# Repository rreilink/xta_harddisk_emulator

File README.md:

# xta_harddisk_emulator
A replacement of old XTA harddisks by USB or SPI-flash storage

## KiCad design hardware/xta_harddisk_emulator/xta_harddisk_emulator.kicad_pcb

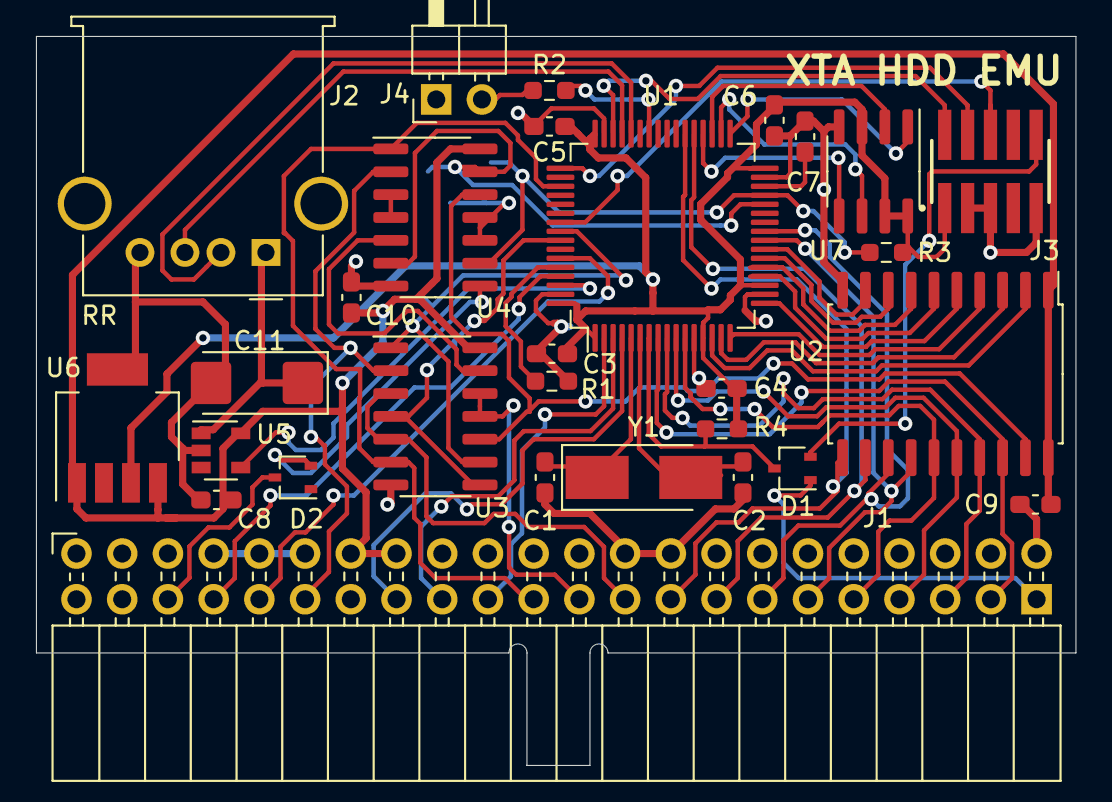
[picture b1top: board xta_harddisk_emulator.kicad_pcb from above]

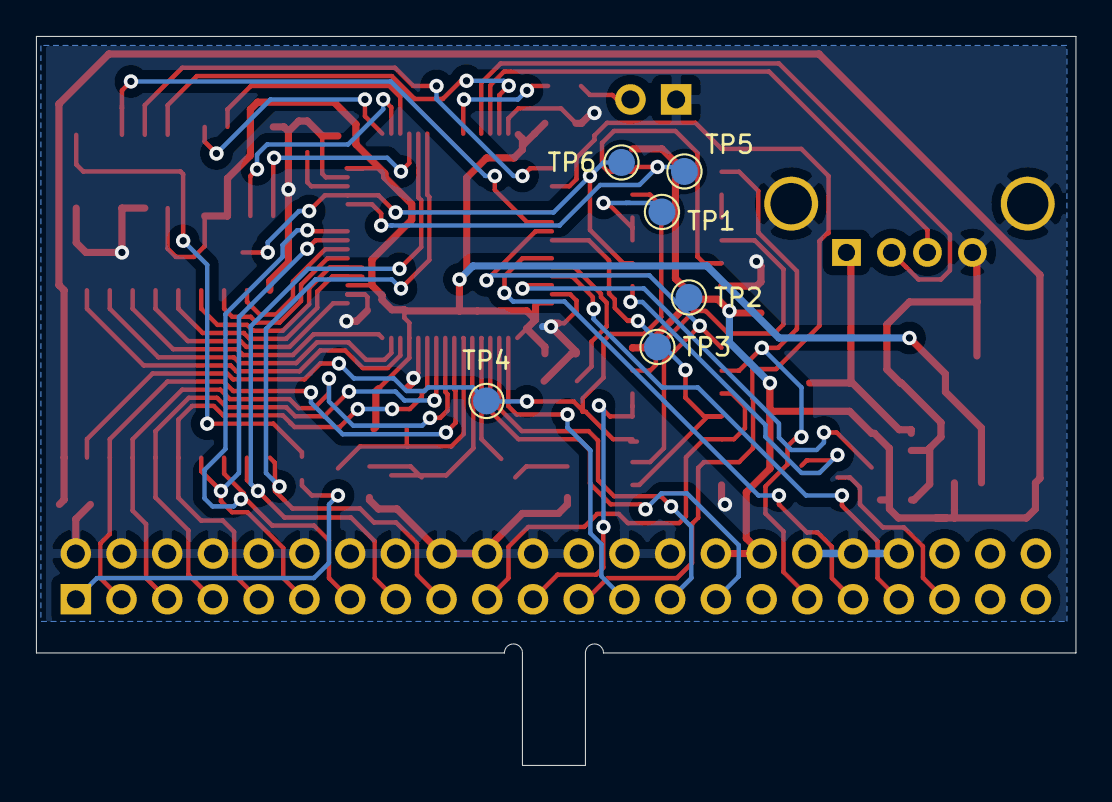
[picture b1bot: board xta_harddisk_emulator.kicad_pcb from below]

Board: 2 copper layers, 57.7 x 40.5 mm, 35 parts (6 on the bottom side), 58 nets.

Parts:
C1, C2: 18pF; C_0603_1608Metric_Pad1.08x0.95mm_HandSolder
C3, C4, C5, C6, C9, C10: 100n; C_0603_1608Metric_Pad1.08x0.95mm_HandSolder
C7, C8: 4.7u; C_0603_1608Metric_Pad1.08x0.95mm_HandSolder
C11: 150u; CP_EIA-6032-28_Kemet-C_Pad2.25x2.35mm_HandSolder
D1, D2: BAT54A; SOT-323_SC-70
J1: Conn_02x22_Odd_Even; PinSocket_2x22_P2.54mm_Horizontal
J2: USB_A; USB_A_Molex_67643_Horizontal
J3: Conn_ARM_JTAG_SWD_10; SAMTEC_FTSH-105-XX-X-DV
J4: Conn_01x02_Male; PinHeader_1x02_P2.54mm_Horizontal
R1, R3, R4: 10k; R_0603_1608Metric_Pad0.98x0.95mm_HandSolder
R2: 220; R_0603_1608Metric_Pad0.98x0.95mm_HandSolder
TP1, TP2, TP3, TP4, TP5, TP6: TestPoint; TestPoint_Pad_D1.5mm
U1: STM32F446RETx; LQFP-64_10x10mm_P0.5mm
U2: 74LS245; SOIC-20W_7.5x12.8mm_P1.27mm
U3: 7402; SOIC-14_3.9x8.7mm_P1.27mm
U4: 7400; SOIC-14_3.9x8.7mm_P1.27mm
U5: TPS2051B; SOT-23-5
U6: LP38693MP-3.3; SOT-223-5
U7: S25FL127SABMFI101; SOIC-8_3.9x4.9mm_P1.27mm
Y1: 8MHz; Crystal_SMD_5032-2Pin_5.0x3.2mm_HandSoldering

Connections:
+3V3: C3.1, C4.1, C5.1, C6.1, J3.1, R3.1, R4.2, U1.1, U1.13, U1.19, U1.32, U1.48, U1.64, U6.3, U7.3, U7.7, U7.8
/A0: J1.25, U1.2
/A1: J1.27, U1.3
/A2: J1.29, U1.4
/ACCESS: TP1.1, U4.10, U4.11
/D0: J1.3, U1.8, U2.18
/D1: J1.5, U1.9, U2.17
/D2: J1.7, U1.10, U2.16
/D3: J1.9, U1.11, U2.15
/D4: J1.11, U1.24, U2.14
/D5: J1.13, U1.25, U2.13
/D6: J1.15, U1.37, U2.12
/D7: J1.17, U1.38, U2.11
/DRQ: J1.35, U1.59
/HOST_nRST: D1.1, J1.1
/IOCHRDY: D2.3, J1.39
/IRQ: J1.37, U1.61
/RD_DMA: TP2.1, U1.56, U3.1, U3.9
/RD_REG: TP3.1, U1.57, U3.4, U3.8
/SWCLK: J3.4, U1.49
/SWD_nRST: D1.2, J3.10
/SWIO: J3.2, U1.46
/SWO: J3.6, U1.55
/VUSB_ENA: U1.62, U5.4
/V_USB: C11.1, J2.1, U5.1
/nCS: J1.23, U1.51, U3.6, U4.1
/nDACK: J1.33, U3.2, U4.2
/nIORD: J1.19, U3.3, U3.5
/nIOWR: J1.21, U3.11, U3.12
/nIO_RDY: R3.2, TP6.1, U1.29, U4.9
/nRD: TP4.1, U2.19, U3.10, U4.12
/nWR: TP5.1, U1.28, U4.6, U4.13
GND: C1.2, C2.2, C3.2, C4.2, C5.2, C6.2, C7.2, C8.2, C9.2, C10.2, C11.2, J1.2, J1.4, J1.6, J1.8, J1.10, J1.12, J1.14, J1.16, J1.18, J1.20, J1.22, J1.24, J1.26, J1.28, J1.34, J1.36, J1.38, J2.4, J2.5, J3.3, J3.5, J3.9, J4.1, R1.2, U1.12, U1.18, U1.31, U1.47, U1.63, U2.10, U3.7, U4.7, U5.2, U6.5, U7.4
unnamed: C1.1, U1.5, Y1.1
unnamed: C2.1, U1.6, Y1.2
unnamed: C7.1, U1.30
unnamed: D1.3, R4.1, U1.7
unnamed: D2.2, U4.8
unnamed: J2.2, U1.44
unnamed: J2.3, U1.45
unnamed: J4.2, R2.1
unnamed: R1.1, U1.60
unnamed: R2.2, U1.42
unnamed: U1.14, U2.2
unnamed: U1.15, U2.3
unnamed: U1.16, U2.4
unnamed: U1.17, U2.5
unnamed: U1.20, U2.6
unnamed: U1.21, U2.7
unnamed: U1.22, U2.8
unnamed: U1.23, U2.9
unnamed: U1.33, U7.1
unnamed: U1.34, U7.6
unnamed: U1.35, U7.2
unnamed: U1.36, U7.5
unnamed: U3.13, U4.5
unnamed: U4.3, U4.4
VCC: C8.1, C9.1, C10.1, J1.30, J1.32, U2.1, U2.20, U3.14, U4.14, U5.5, U6.1, U6.4

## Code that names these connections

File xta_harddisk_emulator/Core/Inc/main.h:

/* USER CODE BEGIN Header */
/**
  ******************************************************************************
  * @file           : main.h
  * @brief          : Header for main.c file.
  *                   This file contains the common defines of the application.
  ******************************************************************************
  * @attention
  *
  * <h2><center>&copy; Copyright (c) 2021 STMicroelectronics.
  * All rights reserved.</center></h2>
  *
  * This software component is licensed by ST under BSD 3-Clause license,
  * the "License"; You may not use this file except in compliance with the
  * License. You may obtain a copy of the License at:
  *                        opensource.org/licenses/BSD-3-Clause
  *
  ******************************************************************************
  */
/* USER CODE END Header */

/* Define to prevent recursive inclusion -------------------------------------*/
#ifndef __MAIN_H
#define __MAIN_H

#ifdef __cplusplus
extern "C" {
#endif

/* Includes ------------------------------------------------------------------*/
#include "stm32f4xx_hal.h"

/* Private includes ----------------------------------------------------------*/
/* USER CODE BEGIN Includes */

/* USER CODE END Includes */

/* Exported types ------------------------------------------------------------*/
/* USER CODE BEGIN ET */

/* USER CODE END ET */

/* Exported constants --------------------------------------------------------*/
/* USER CODE BEGIN EC */

/* USER CODE END EC */

/* Exported macro ------------------------------------------------------------*/
/* USER CODE BEGIN EM */

/* USER CODE END EM */

/* Exported functions prototypes ---------------------------------------------*/
void Error_Handler(void);

/* USER CODE BEGIN EFP */

/* USER CODE END EFP */

/* Private defines -----------------------------------------------------------*/
#define B1_Pin GPIO_PIN_13
#define B1_GPIO_Port GPIOC
#define D0_Pin GPIO_PIN_0
#define D0_GPIO_Port GPIOC
#define D1_Pin GPIO_PIN_1
#define D1_GPIO_Port GPIOC
#define D2_Pin GPIO_PIN_2
#define D2_GPIO_Port GPIOC
#define D3_Pin GPIO_PIN_3
#define D3_GPIO_Port GPIOC
#define USART_TX_Pin GPIO_PIN_2
#define USART_TX_GPIO_Port GPIOA
#define USART_RX_Pin GPIO_PIN_3
#define USART_RX_GPIO_Port GPIOA
#define LD2_Pin GPIO_PIN_5
#define LD2_GPIO_Port GPIOA
#define D4_Pin GPIO_PIN_4
#define D4_GPIO_Port GPIOC
#define D5_Pin GPIO_PIN_5
#define D5_GPIO_Port GPIOC
#define RD_REG_Pin GPIO_PIN_0
#define RD_REG_GPIO_Port GPIOB
#define RD_REG_EXTI_IRQn EXTI0_IRQn
#define nWR_Pin GPIO_PIN_1
#define nWR_GPIO_Port GPIOB
#define nWR_EXTI_IRQn EXTI1_IRQn
#define RD_DMA_Pin GPIO_PIN_2
#define RD_DMA_GPIO_Port GPIOB
#define RD_DMA_EXTI_IRQn EXTI2_IRQn
#define DEBUG_Pin GPIO_PIN_12
#define DEBUG_GPIO_Port GPIOB
#define USB_VBUS_ENA_Pin GPIO_PIN_13
#define USB_VBUS_ENA_GPIO_Port GPIOB
#define DEBUG2_Pin GPIO_PIN_14
#define DEBUG2_GPIO_Port GPIOB
#define DEBUG3_Pin GPIO_PIN_15
#define DEBUG3_GPIO_Port GPIOB
#define D6_Pin GPIO_PIN_6
#define D6_GPIO_Port GPIOC
#define D7_Pin GPIO_PIN_7
#define D7_GPIO_Port GPIOC
#define A0_Pin GPIO_PIN_8
#define A0_GPIO_Port GPIOC
#define A1_Pin GPIO_PIN_9
#define A1_GPIO_Port GPIOC
#define TMS_Pin GPIO_PIN_13
#define TMS_GPIO_Port GPIOA
#define TCK_Pin GPIO_PIN_14
#define TCK_GPIO_Port GPIOA
#define A2_Pin GPIO_PIN_10
#define A2_GPIO_Port GPIOC
#define nDACK_Pin GPIO_PIN_11
#define nDACK_GPIO_Port GPIOC
#define nIORD_Pin GPIO_PIN_12
#define nIORD_GPIO_Port GPIOC
#define SWO_Pin GPIO_PIN_3
#define SWO_GPIO_Port GPIOB
#define nIORDY_Pin GPIO_PIN_4
#define nIORDY_GPIO_Port GPIOB
#define DRQ_Pin GPIO_PIN_8
#define DRQ_GPIO_Port GPIOB
#define IRQ_Pin GPIO_PIN_9
#define IRQ_GPIO_Port GPIOB
/* USER CODE BEGIN Private defines */

/* USER CODE END Private defines */

#ifdef __cplusplus
}
#endif

#endif /* __MAIN_H */

/************************ (C) COPYRIGHT STMicroelectronics *****END OF FILE****/

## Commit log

2021-03-30 Initial minimally working code presents a single sector which contains boot code to print a single letter ‘R’
2021-03-30 Refactoring: move XTA interface to a separate compile unit
2021-04-06 Add XT-Attachment interface documentation
2021-04-09 Added USB host hardware driver + middleware; connected xta code to USB. Working read/write access; booting from USB working
2021-04-13 Changed microcontroller to STM32F446
2021-04-21 Updated configuration for STM32F446
2022-01-23 Modified HW with three different interrupts: register IO read, DMA read and write (both register IO and DMA)
    Working read acces + booting
2022-03-08 added hardware design
2022-03-08 firmware working prototype
